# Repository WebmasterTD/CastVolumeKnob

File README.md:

# CastVolumeKnob

is hardware volume control for Chromecast Audio devices, based on the ESP8266 microcontroller using micropython.

## The problem

For controlling the volume on Chromecast devices you need to use your phone. - it is clumsy, not very intuitive.

## The requirements

* Easy to use, hardware based volume control.
* Wireless
* Visual feedback of the current volume level
* Relatively cheap

## The solution

This is the final form. Completely wireless, rechargeable device. 

To wake it up you have to tap the knob once. After it wakes up it automatically connects to the first chromecast device, you can control its volume by turning the knob. To change the device tap the knob again. To stop the music playback press and hold the knob until the LEDs turn red.

## Instructions:

### Schematic

### Programming the ESP8266

* install esptool and ampy
    ```shell
    pip install esptool
    pip install adafruit-ampy
    ```

* erase the flash with esptool
    ```shell
    esptool.py --port COM5 erase_flash
    ```
* download the micropython firmware

    [MicroPython](http://micropython.org/download#esp8266)

* deploy the firmware
    ```shell
    esptool.py --port COM5 --baud 460800 write_flash --flash_size=detect 0 esp8266-20170108-v1.8.7.bin
    ```

* Configuring wificonf.py

* put the code to the mcu
    ```shell
    ampy -p COM5 -b 115200 put     main.py
                    boot.py
                    encoder.py
                    wificonf.py
                    volume.py
    ```

### Assembly

* 3D print the case and glue the middle and the top part together
* Solder everything to the PCB
* Put the LED ring and Encoder in place
* Screw the Board in place
* Solder the Battery holder to the charging/boost converter board
* Glue it in place
* Screw the bottom part in

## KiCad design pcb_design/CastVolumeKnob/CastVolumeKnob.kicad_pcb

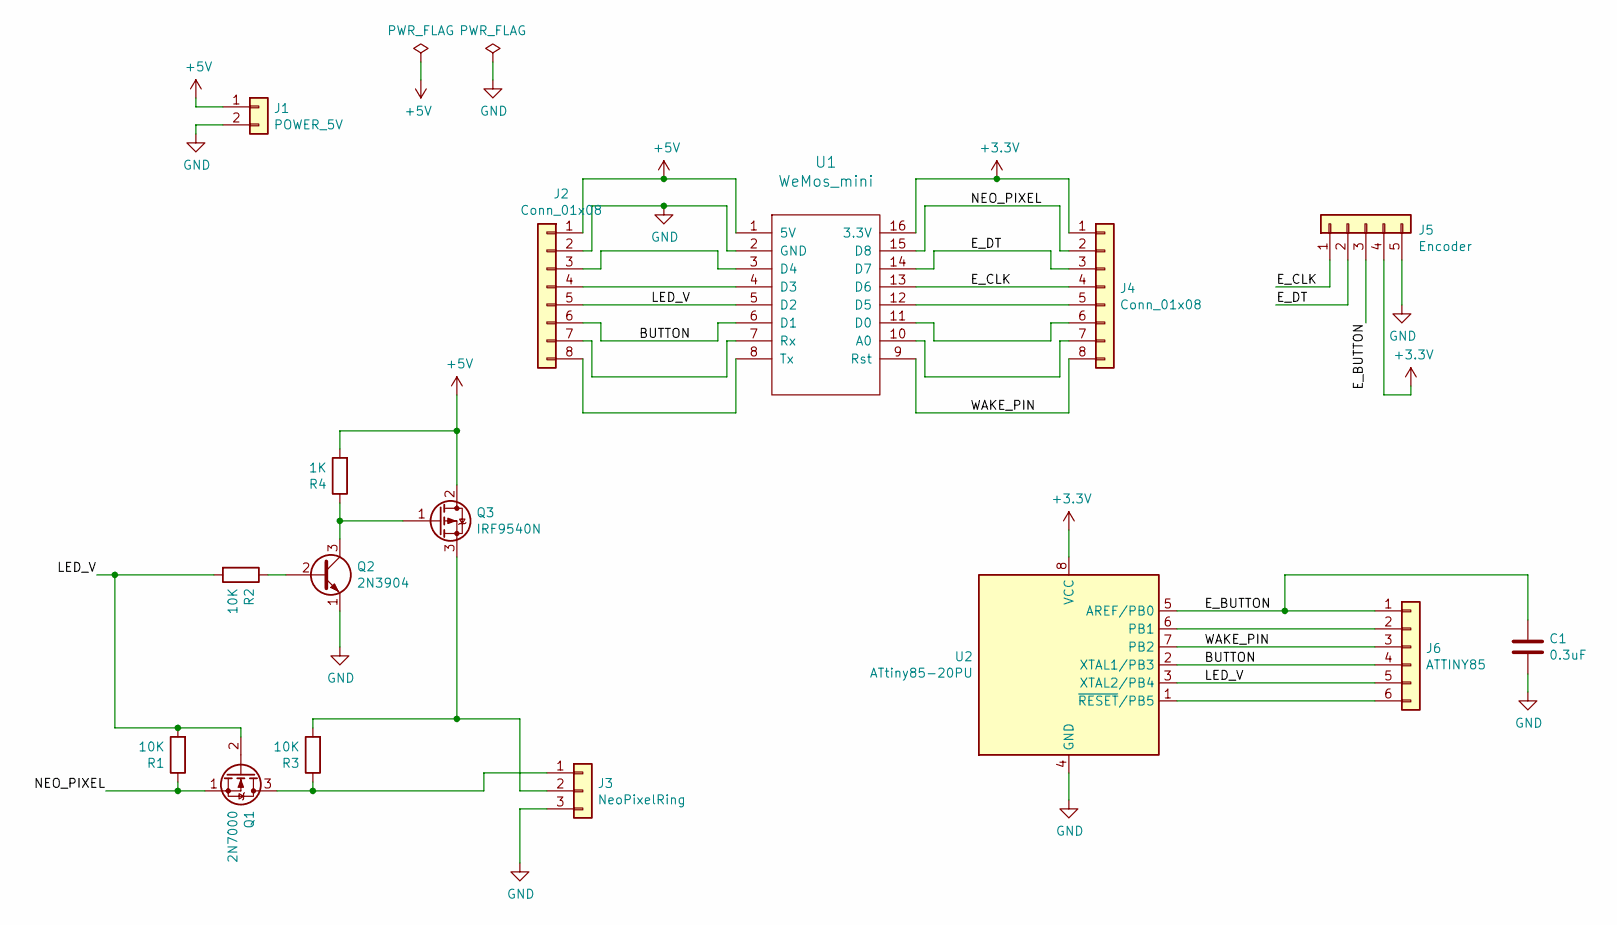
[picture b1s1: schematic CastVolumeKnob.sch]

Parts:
C1: 0.3uF; C_Disc_D3.8mm_W2.6mm_P2.50mm
J1: POWER_5V; PinHeader_1x02_P2.54mm_Horizontal
J2, J4: Conn_01x08; PinHeader_1x08_P2.54mm_Vertical
J3: NeoPixelRing; PinHeader_1x03_P2.54mm_Horizontal
J5: Encoder; PinHeader_1x05_P2.54mm_Horizontal
J6: ATTINY85; PinHeader_1x06_P2.54mm_Vertical
Q1: 2N7000; TO-92_Inline
Q2: 2N3904; TO-92_Inline
Q3: IRF9540N; TO-220-3_Horizontal_TabDown-132
R1, R2, R3: 10K; R_Axial_DIN0207_L6.3mm_D2.5mm_P10.16mm_Horizontal
R4: 1K; R_Axial_DIN0207_L6.3mm_D2.5mm_P10.16mm_Horizontal
U1: WeMos_mini; wemos-d1-mini-connectors-only
U2: ATtiny85-20PU; DIP-8_W7.62mm_Socket_LongPads

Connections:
+3V3: J4.1, J5.4, U1.16 (3.3V), U2.8 (VCC)
+5V: J1.1, J2.1, Q3.2 (D), R4.2, U1.1 (5V)
/BUTTON: J2.6, J6.4, U1.6 (D1), U2.2 (XTAL1/PB3)
/E_BUTTON: C1.1, J5.3, J6.1, U2.5 (AREF/PB0)
/E_CLK: J4.4, J5.1, U1.13 (D6)
/E_DT: J4.3, J5.2, U1.14 (D7)
/LED_V: J2.5, J6.5, Q1.2 (G), R1.2, R2.2, U1.5 (D2), U2.3 (XTAL2/PB4)
/NEO_PIXEL: J4.2, Q1.1 (S), R1.1, U1.15 (D8)
/WAKE_PIN: J4.8, J6.3, U1.9 (Rst), U2.7 (PB2)
GND: C1.2, J1.2, J2.2, J3.3, J5.5, Q2.1 (E), U1.2 (GND), U2.4 (GND)
unnamed: J2.3, U1.3 (D4)
unnamed: J2.4, U1.4 (D3)
unnamed: J2.7, U1.7 (Rx)
unnamed: J2.8, U1.8 (Tx)
unnamed: J3.1, Q1.3 (D), R3.1
unnamed: J3.2, Q3.3 (S), R3.2
unnamed: J4.5, U1.12 (D5)
unnamed: J4.6, U1.11 (D0)
unnamed: J4.7, U1.10 (A0)
unnamed: J6.2, U2.6 (PB1)
unnamed: J6.6, U2.1 (~RESET~/PB5)
unnamed: Q2.2 (B), R2.1
unnamed: Q2.3 (C), Q3.1 (G), R4.1

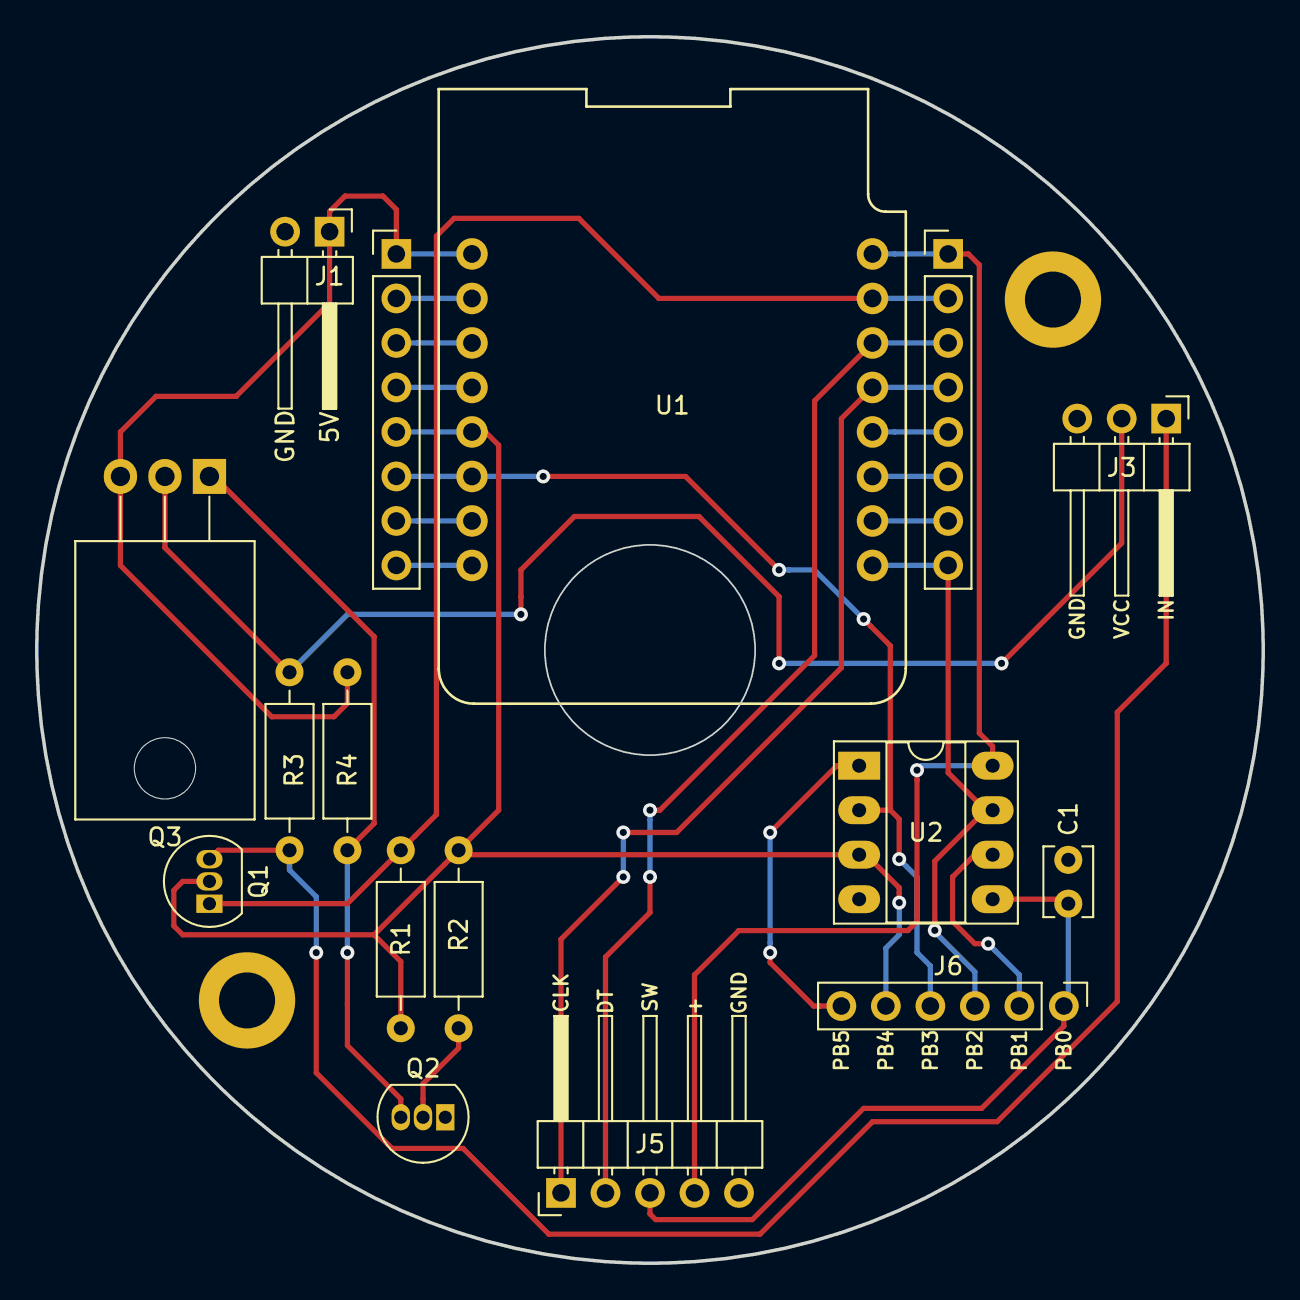
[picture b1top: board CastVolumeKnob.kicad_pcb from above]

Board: 2 copper layers, 70.0 x 70.0 mm, 16 parts (0 on the bottom side), 23 nets.

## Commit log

2018-09-23 added /
2018-09-23 added README.md
2018-10-01 added test2.py
2018-10-02 volume message size tests
2018-10-04 Working version
2018-10-06 added esp8266 main code
2018-10-08 added esp encoder library
2018-10-08 updated gitignore
2018-10-23 added TODO list
2018-10-26 added wifi config
2018-10-29 added set fuction to encoder
2018-10-29 Chromecast class created
2018-10-29 small changes
2018-11-02 reorganized folder structure
2018-11-04 added led indicators
2018-11-04 basic arduino interrupt
2018-11-07 small change
2018-11-07 KiCaD project created
2018-11-08 set_val fixes
2018-11-11 arduino interrupt wake up
2018-11-11 NeoPixelRing Class
2018-11-11 Cleaned up code, MOSFET led switch
2018-11-11 KiCad schematic changes
2018-11-11 Kicad on linux
2018-11-14 led Mosfet control baked into neo pixel class
2018-11-14 Improved schematics
2018-11-18 Interrupt misfiring fix
2018-11-18 schematic fixes
2018-11-25 Working version on ATTINY85
2018-11-25 PCB schematic changes
2018-11-29 volume init bug fixed
2018-12-02 Added switch button mode
2018-12-02 Button switch test
2018-12-02 PCB v01 - oredered version
2018-12-04 removed unnecessary tests
2018-12-08 switch between chromecasts with encoder button
2018-12-09 change device color
2018-12-16 New colors and animations
2018-12-20 Added button press time
2018-12-20 sessionid found to STOP
2018-12-21 stop fuction (not fully working)
2018-12-21 Fixed STOP function
2018-12-23 WORKING VERSION static ip, bug fixes
2019-01-01 Fixed mosfet footprint for v2 pcb
2019-01-20 Working version 1.0
2019-01-27 Added Brightness control
2019-01-27 Added 3D files and README
2019-01-30 Updated Schematic
2019-01-30 JPG Schematic
2019-01-30 Fixed image paths
2019-06-16 White light at wifi connection
2019-10-07 add .pdf of schematic and layout
2019-12-02 Updated requrements.txt
